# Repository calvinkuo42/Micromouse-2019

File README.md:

# Micromouse-2019

IEEE Micromouse project I did with Philip Kwan and Sean Chen at UCLA over the 2018-19 school year. We began with a STM32 Nucleo Development board and assembled a demo from a previously designed kit. We then programmed the hardware using C on mbed. A similar code was used to control the "mouse" we later designed ourselves (schematic and board).

Micromouse: https://en.wikipedia.org/wiki/Micromouse

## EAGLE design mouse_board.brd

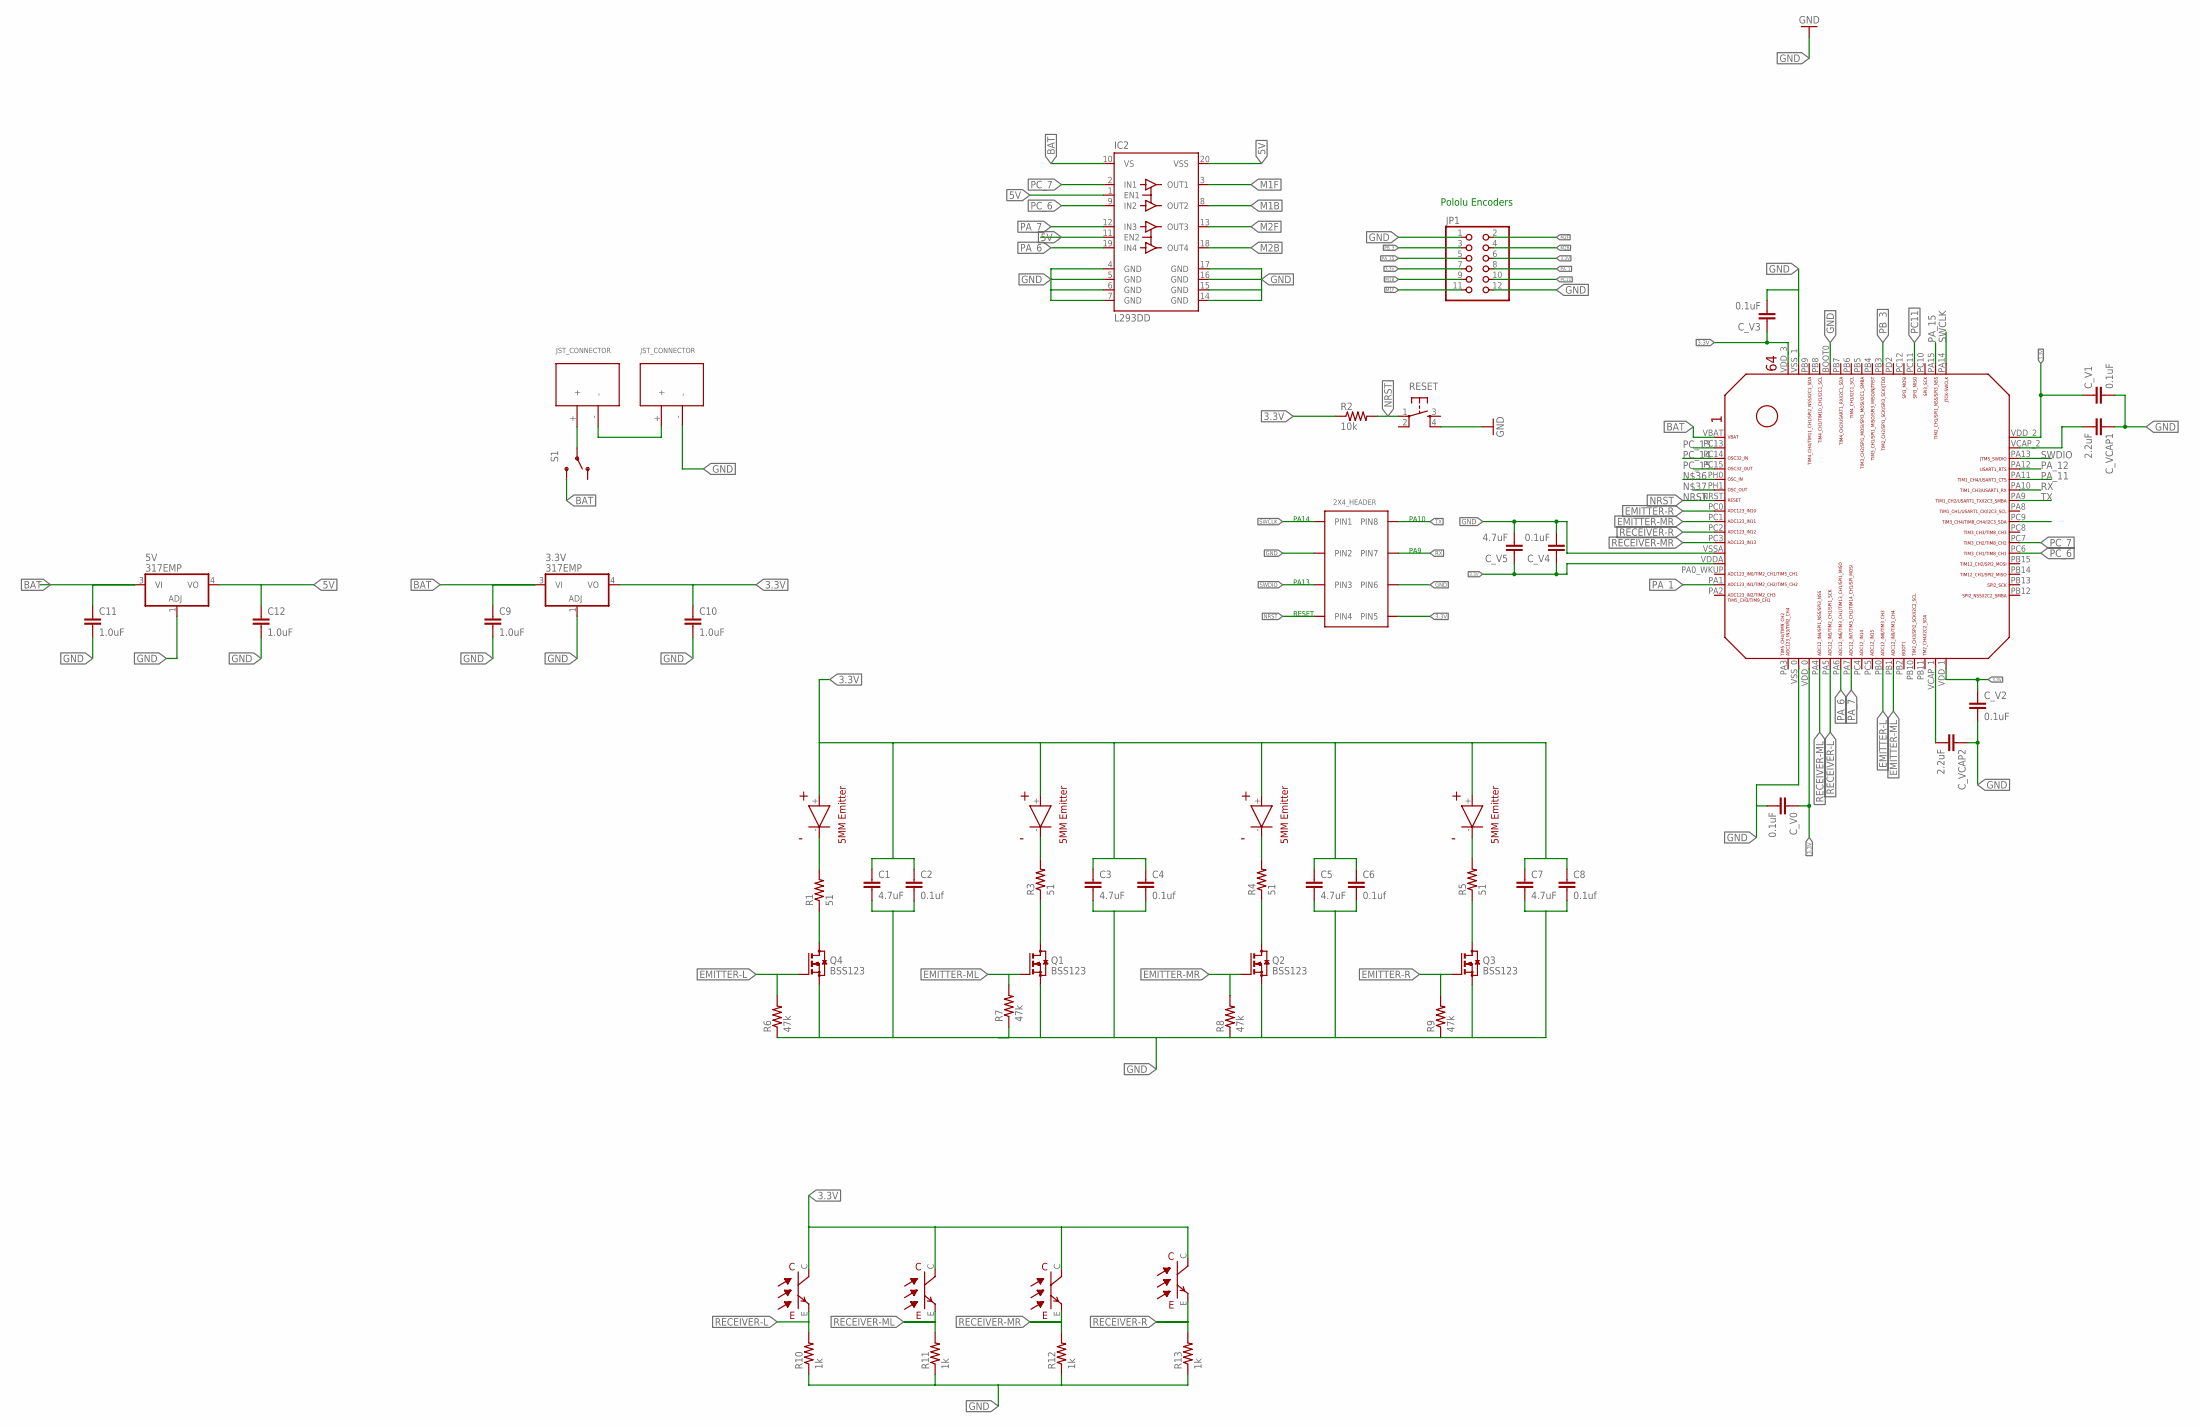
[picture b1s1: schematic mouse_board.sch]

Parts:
3.3V, 5V: 317EMP; SOT223
BATTERY1, BATTERY2: JST_CONNECTOR_FEMALE
C1, C3, C5, C7: 4.7uF; 0603-CAP
C2, C4, C6, C8: 0.1uf; 0603-CAP
C9, C10, C11, C12: 1.0uF; 0603-CAP
C_V0, C_V1, C_V2, C_V3, C_V4: 0.1uF; 0603-CAP
C_V5: 4.7uF; 0603-CAP
C_VCAP1, C_VCAP2: 2.2uF; 0603-CAP
IC2: L293DD; SO20
JP1: PINHD-2X6; 2X06
MCU/BLU: 2X3_HEADER
Q1, Q2, Q3, Q4: BSS123; SOT23
R1, R3, R4, R5: 51; 0603-RES
R2: 10k; 0603-RES
R6, R7, R8, R9: 47k; 0603-RES
R10, R11, R12, R13: 1k; 0603-RES
RESET: TAC_SWITCHPTH; TACTILE-PTH
S1: SWITCH-SPST-SMD-A
U$1: STM32F405/415_LQFP64
U$2, U$3, U$4, U$5: EMITTER
U$6, U$7, U$8, U$9: RECEIVER

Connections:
3.3V: 3.3V.4 (VO), C1.1, C2.1, C7.1, C8.1, C10.1, C_V0.1, C_V1.1, C_V2.1, C_V3.1, C_V4.1, C_V5.1, JP1.6, JP1.7, MCU/BLU.PIN5, R2.1, U$1.VDDA, U$1.VDD_0, U$1.VDD_1, U$1.VDD_2, U$1.VDD_3, U$2.+, U$3.+, U$4.+, U$5.+, U$6.C, U$7.C, U$8.C, U$9.C
3.3V1: Q4.3 (D), R1.1
3.3V2: Q1.3 (D), R3.1
3.3V4: Q3.3 (D), R5.1
5V: 5V.4 (VO), C12.1, IC2.1 (EN1), IC2.11 (EN2), IC2.20 (VSS)
5V1: C3.1, C4.1
5V2: C5.1, C6.1
BAT: 3.3V.3 (VI), 5V.3 (VI), C9.1, C11.1, IC2.10 (VS), S1.3 (S), U$1.VBAT
EMITTER-L: Q4.1 (G), R6.2, U$1.PB0
EMITTER-L2: R11.2, U$7.E
EMITTER-L3: R12.2, U$8.E
EMITTER-L4: R13.2, U$9.E
EMITTER-ML: Q1.1 (G), R7.2, U$1.PB1
EMITTER-MR: Q2.1 (G), R8.2, U$1.PC1
EMITTER-R: Q3.1 (G), R9.2, U$1.PC0
GND: 3.3V.1 (ADJ), 5V.1 (ADJ), BATTERY2.-, C1.2, C2.2, C3.2, C4.2, C5.2, C6.2, C7.2, C8.2, C9.2, C10.2, C11.2, C12.2, C_V0.2, C_V1.2, C_V2.2, C_V3.2, C_V4.2, C_V5.2, C_VCAP1.1, C_VCAP2.1, IC2.4 (GND), IC2.5 (GND), IC2.6 (GND), IC2.7 (GND), IC2.14 (GND), IC2.15 (GND), IC2.16 (GND), IC2.17 (GND), JP1.1, JP1.12, MCU/BLU.PIN2, MCU/BLU.PIN6, Q1.2 (S), Q2.2 (S), Q3.2 (S), Q4.2 (S), R6.1, R7.1, R8.1, R9.1, R10.1, R11.1, R12.1, R13.1, RESET.4, U$1.BOOT0, U$1.VSSA, U$1.VSS_0, U$1.VSS_1
M1B: IC2.8 (OUT2), JP1.9
M1F: IC2.3 (OUT1), JP1.11
M2B: IC2.18 (OUT4), JP1.4
M2F: IC2.13 (OUT3), JP1.2, U$1.PC9
unnamed: R1.2, U$5.-
unnamed: R3.2, U$4.-
unnamed: R4.2, U$3.-
unnamed: R5.2, U$2.-
unnamed: Q2.3 (D), R4.1
unnamed: BATTERY1.-, BATTERY2.+
unnamed: BATTERY1.+, S1.2
NRST: MCU/BLU.PIN4, R2.2, RESET.1, U$1.NRST
PA_1: JP1.8, U$1.PA1
PA_6: IC2.19 (IN4), U$1.PA6
PA_7: IC2.12 (IN3), U$1.PA7
PA_11: U$1.PA11
PA_12: U$1.PA12
PA_15: JP1.5, U$1.PA15
PB_3: JP1.3, U$1.PB3
PC11: JP1.10, U$1.PC11
PC_6: IC2.9 (IN2), U$1.PC6
PC_7: IC2.2 (IN1), U$1.PC7
PC_13: U$1.PC13
PC_14: U$1.PC14
PC_15: U$1.PC15
RECEIVER-L: R10.2, U$1.PA5, U$6.E
RECEIVER-ML: U$1.PA4
RECEIVER-MR: U$1.PC3
RECEIVER-R: U$1.PC2
RX: MCU/BLU.PIN7, U$1.PA10
SWCLK: MCU/BLU.PIN1, U$1.PA14
SWDIO: MCU/BLU.PIN3, U$1.PA13
TX: MCU/BLU.PIN8, U$1.PA9
V_C1: C_VCAP1.2, U$1.VCAP_2
V_C2: C_VCAP2.2, U$1.VCAP_1

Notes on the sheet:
PA14
PA13
RESET
PA9
PA10
Pololu Encoders

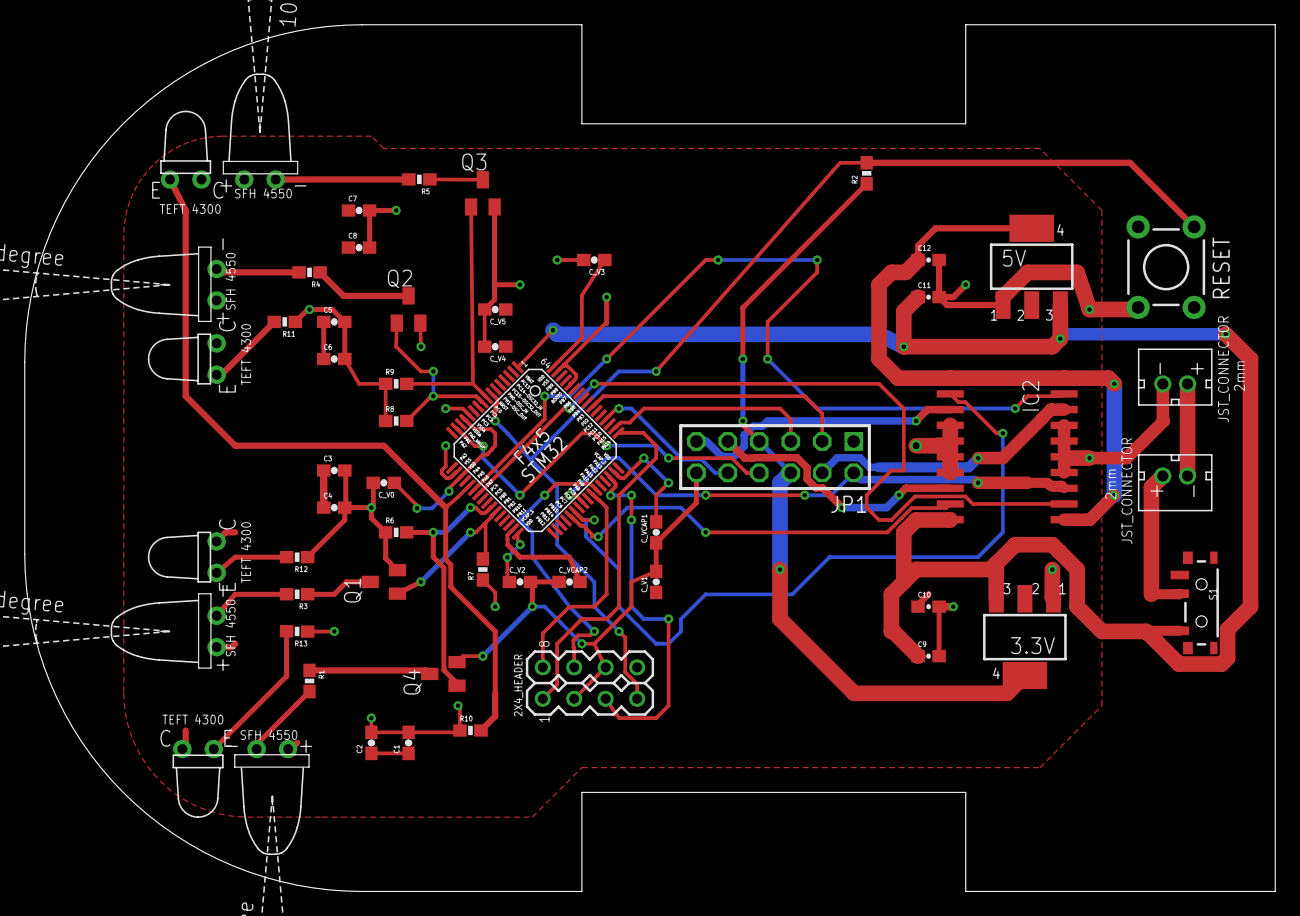
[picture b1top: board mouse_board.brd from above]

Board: 2 copper layers, 101.0 x 70.0 mm, 55 parts (0 on the bottom side), 43 nets.

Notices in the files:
parts and their libraries:
SparkFun: Licensing: CC v3.0 Share-Alike You are welcome to use this library for commercial purposes.
SparkFun-Capacitors: Licensing: Creative Commons ShareAlike 4.0 International - https://creativecommons.org/licenses/by-sa/4.0
